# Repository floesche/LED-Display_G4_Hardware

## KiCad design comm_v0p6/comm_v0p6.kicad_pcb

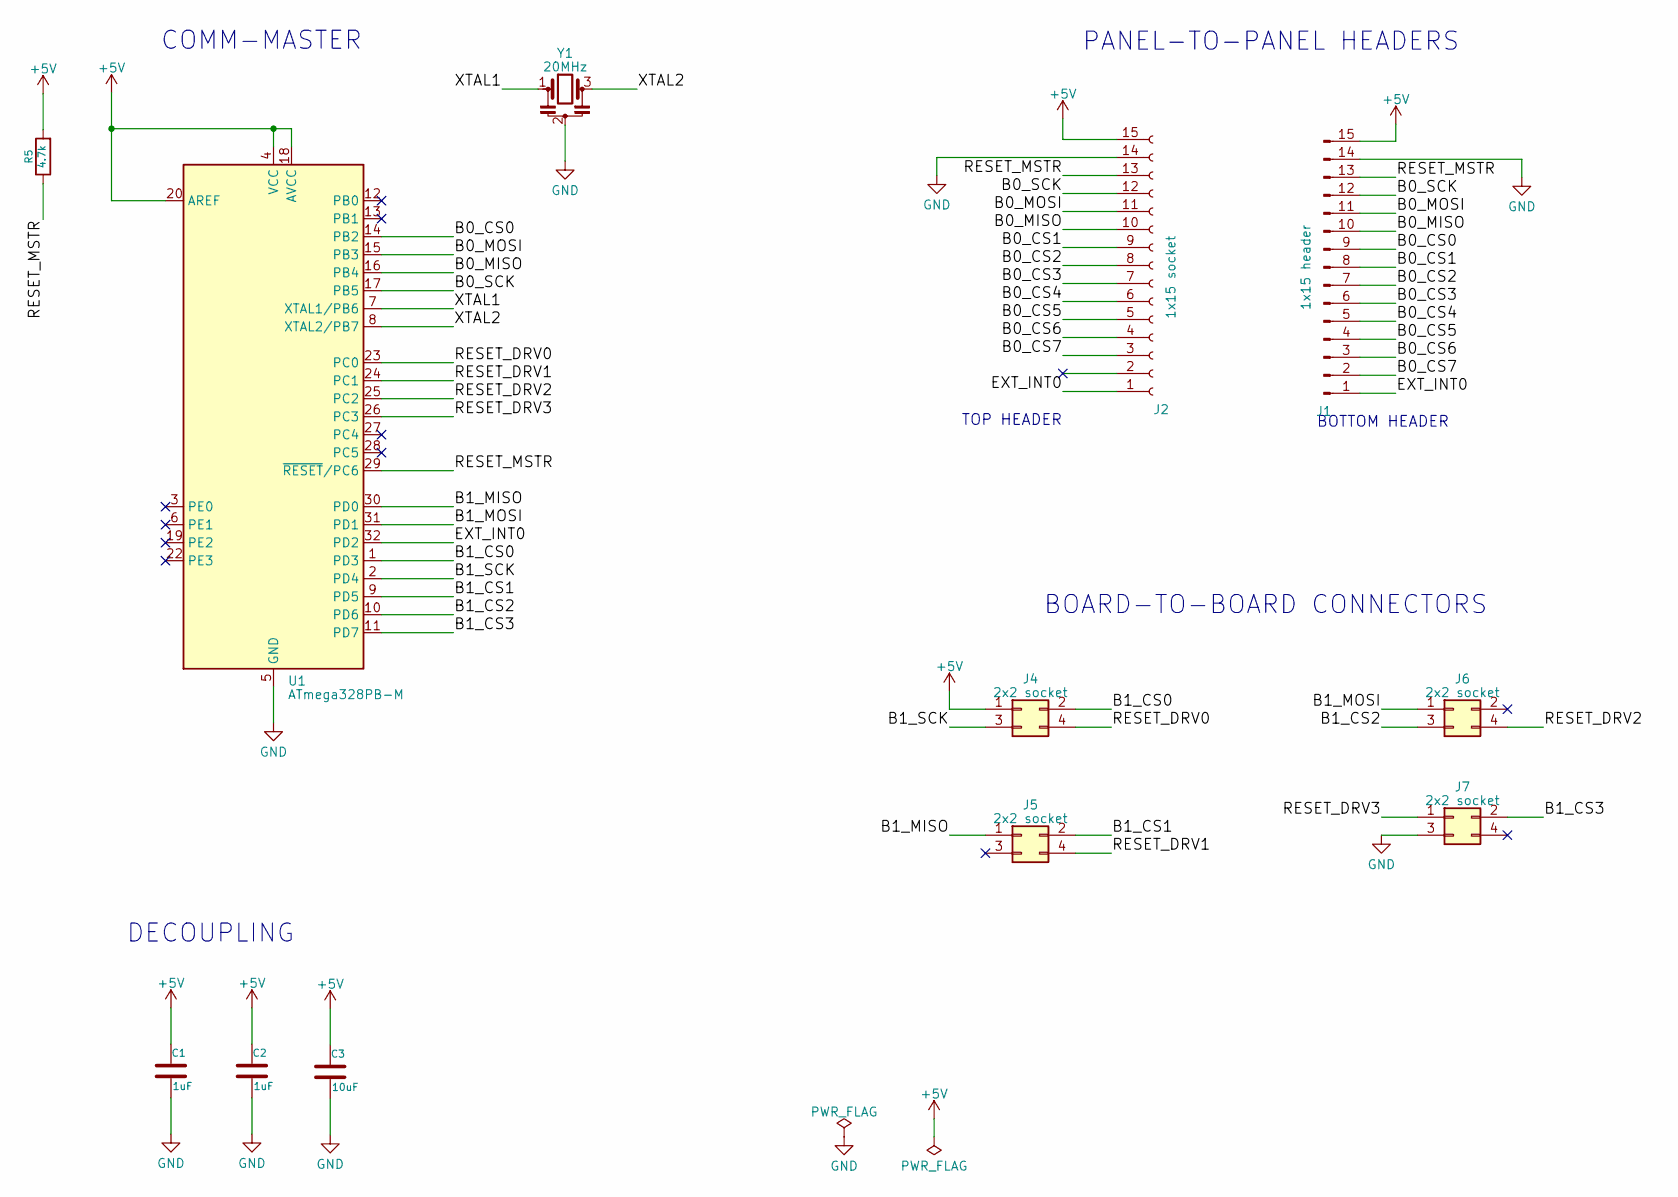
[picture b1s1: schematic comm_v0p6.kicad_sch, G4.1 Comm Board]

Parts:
C1, C2: 1uF; C_0402_1005Metric; DigiKey PN 1276-1067-1-ND
C3: 10uF; C_0805_2012Metric; DigiKey PN 1276-1067-1-ND
J1: 1x15 header; PinHeader_1x15_P2.54mm_Horizontal; DigiKey PN 2057-PH1RB-15-UA-ND
J2: 1x15 socket; PinSocket_1x15_P2.54mm_Horizontal; DigiKey PN 612-SSQ-115-02-G-S-RA-ND
J4, J5, J6, J7: 2x2 socket; PinSocket_2x02_P2.54mm_Vertical; DigiKey PN A125237-ND
R5: 4.7k; R_0603_1608Metric; DigiKey PN 311-4.7KGRCT-ND
U1: ATmega328PB-M; QFN-32-1EP_5x5mm_P0.5mm_EP3.1x3.1mm; DigiKey PN ATMEGA328PB-MURCT-ND
Y1: 20MHz; Resonator_SMD_Murata_CSTxExxV-3Pin_3.0x1.1mm; DigiKey PN 490-17953-1-ND

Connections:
+5V: C1.1, C2.1, C3.1, J1.15, J2.15, J4.1, R5.2, U1.4 (VCC), U1.18 (AVCC), U1.20 (AREF)
/B0_CS0: J1.9, U1.14 (PB2)
/B0_CS1: J1.8, J2.9
/B0_CS2: J1.7, J2.8
/B0_CS3: J1.6, J2.7
/B0_CS4: J1.5, J2.6
/B0_CS5: J1.4, J2.5
/B0_CS6: J1.3, J2.4
/B0_CS7: J1.2, J2.3
/B0_MISO: J1.10, J2.10, U1.16 (PB4)
/B0_MOSI: J1.11, J2.11, U1.15 (PB3)
/B0_SCK: J1.12, J2.12, U1.17 (PB5)
/B1_CS0: J4.2, U1.1 (PD3)
/B1_CS1: J5.2, U1.9 (PD5)
/B1_CS2: J6.3, U1.10 (PD6)
/B1_CS3: J7.2, U1.11 (PD7)
/B1_MISO: J5.1, U1.30 (PD0)
/B1_MOSI: J6.1, U1.31 (PD1)
/B1_SCK: J4.3, U1.2 (PD4)
/EXT_INT0: J1.1, J2.1, U1.32 (PD2)
/RESET_DRV0: J4.4, U1.23 (PC0)
/RESET_DRV1: J5.4, U1.24 (PC1)
/RESET_DRV2: J6.4, U1.25 (PC2)
/RESET_DRV3: J7.1, U1.26 (PC3)
/RESET_MSTR: J1.13, J2.13, R5.1, U1.29 (~RESET/PC6)
/XTAL1: U1.7 (XTAL1/PB6), Y1.1
/XTAL2: U1.8 (XTAL2/PB7), Y1.3
GND: C1.2, C2.2, C3.2, J1.14, J2.14, J7.3, U1.5 (GND), U1.21 (GND), U1.33 (GND), Y1.2

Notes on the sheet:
PANEL-TO-PANEL HEADERS
TOP HEADER
COMM-MASTER
DECOUPLING
BOTTOM HEADER
BOARD-TO-BOARD CONNECTORS

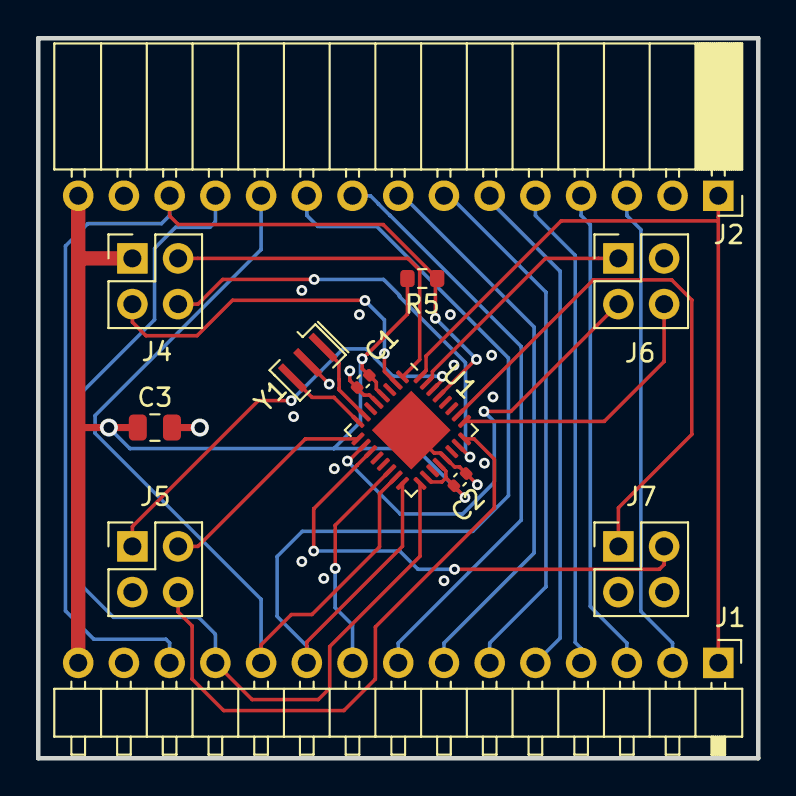
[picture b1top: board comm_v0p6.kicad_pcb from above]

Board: 4 copper layers, 40.0 x 40.0 mm, 12 parts (0 on the bottom side), 28 nets.

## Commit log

2023-09-11 udpate gitignore
2023-09-11 update position file
2023-09-11 remove unrouted temp design
2023-11-17 minor description changes
2023-11-22 add production files for v0p6r2
2023-11-22 cleanup
2024-04-25 remove README from website
2024-07-29 prepare revision 3
2024-10-09 fix CS numbers
2025-08-01 shields for G4 driver and comm board
2025-08-04 make tester ready for order
2025-08-04 export assets
2025-11-13 add schematics, add v0.6 documentation
2025-11-13 update text:
2025-11-13 add 0.4 and 0.5
2026-04-27 update from KiCAD 7 to KiCAD 9
